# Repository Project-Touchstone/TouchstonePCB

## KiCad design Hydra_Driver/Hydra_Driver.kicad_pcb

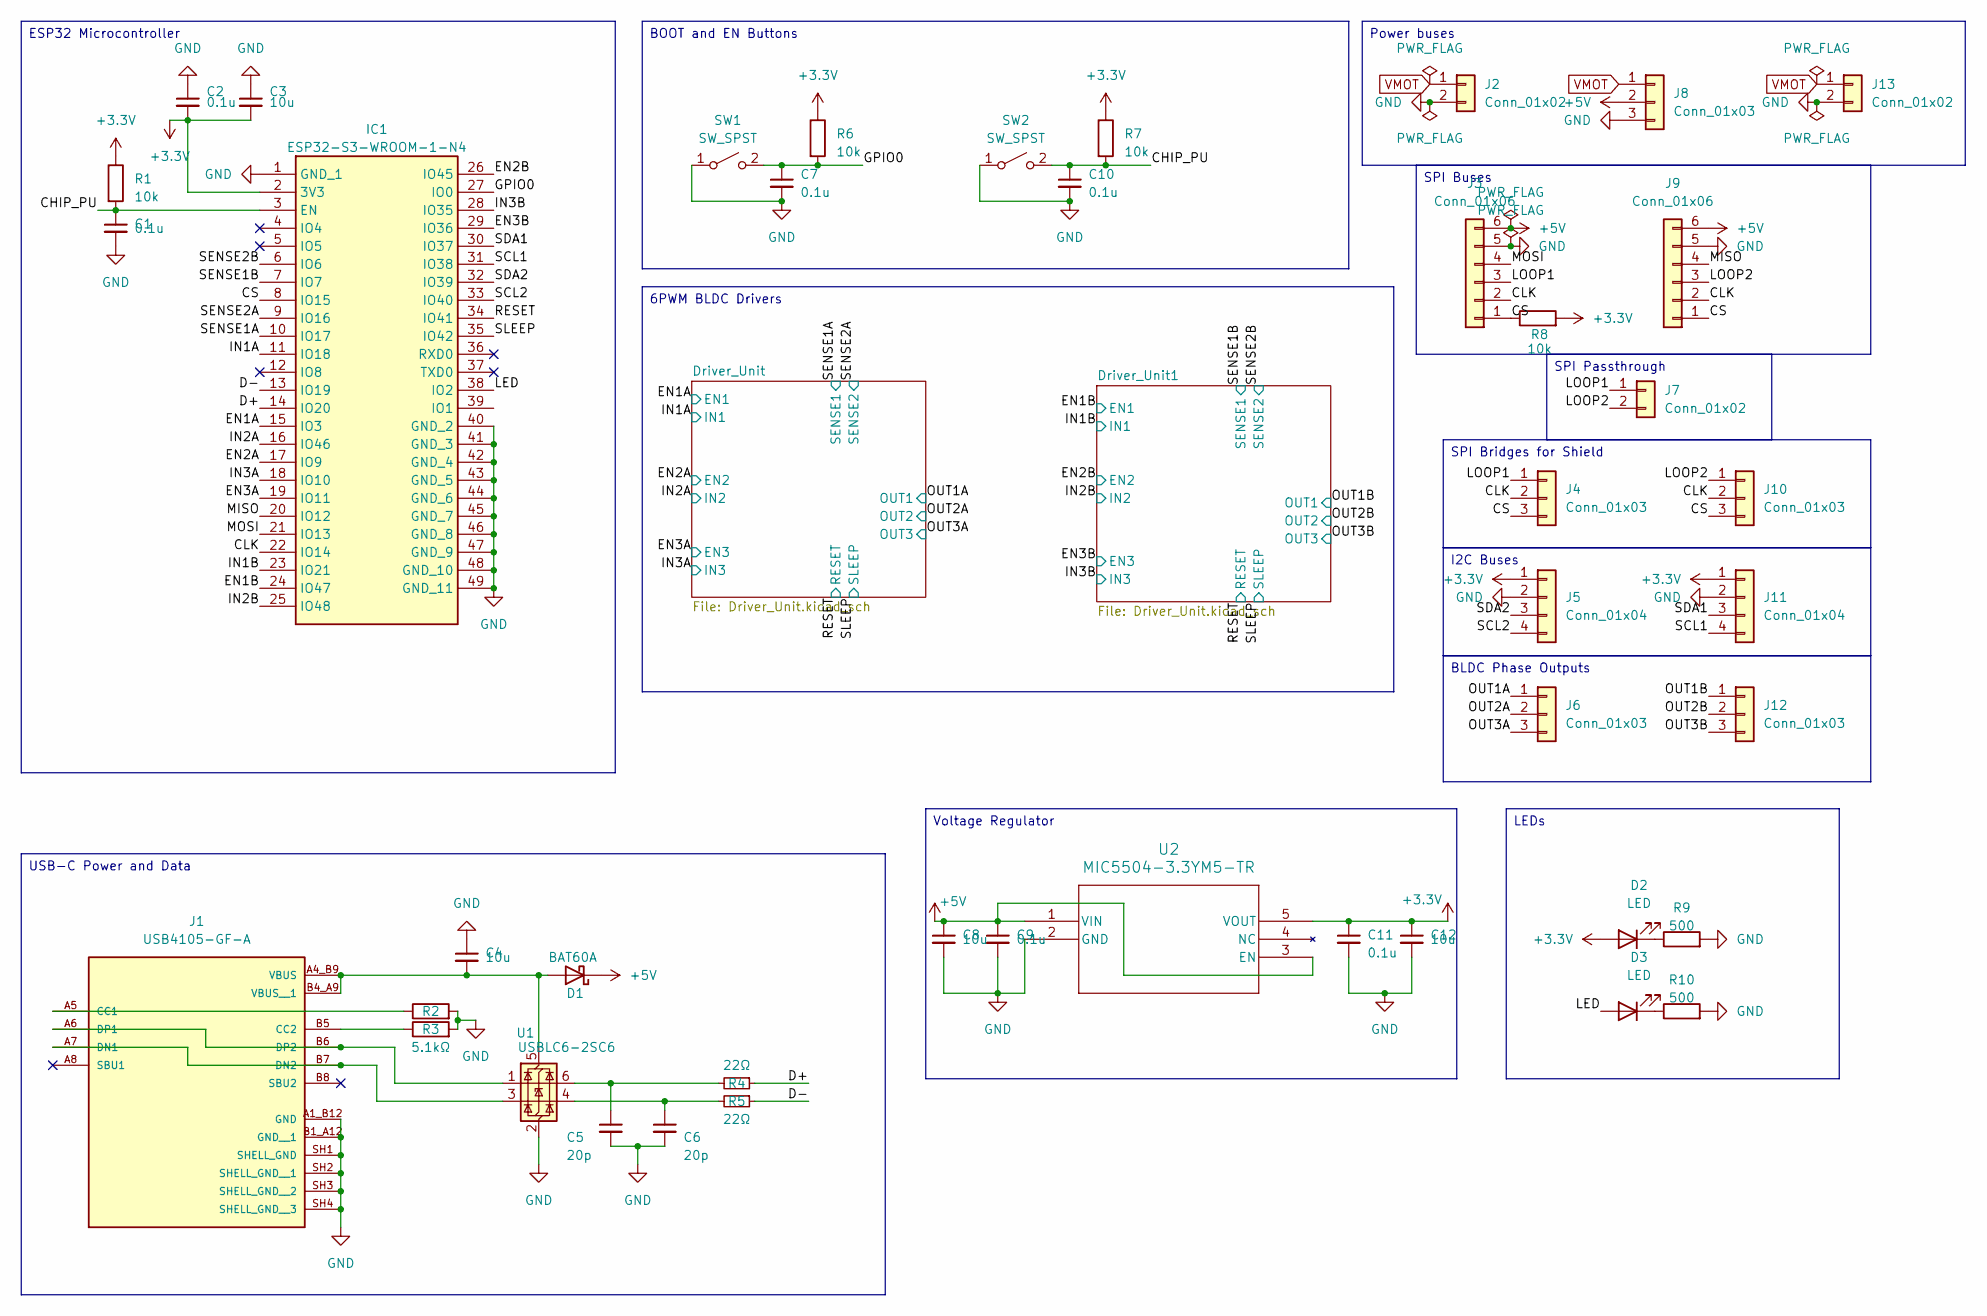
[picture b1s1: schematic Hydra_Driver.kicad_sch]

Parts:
C1, C2, C7, C9, C10, C11: 0.1u; C_0402_1005Metric
C3, C4, C8, C12: 10u; C_0805_2012Metric
C5, C6: 20p; C_0402_1005Metric; LCSC C1648
D1: BAT60A; D_SOD-323; JLCPCB C124187
D2, D3: LED; LED_0603_1608Metric
IC1: ESP32-S3-WROOM-1-N4; ESP32S3WROOM1N4; Manufacturer_Part_Number ESP32-S3-WROOM-1-N4; Mouser Part Number 356-ESP32-S3WROOM1N4
J1: USB4105-GF-A; GCT_USB4105-GF-A; PARTREV B4
J2, J13: Conn_01x02; TerminalBlock_MaiXu_MX126-5.0-02P_1x02_P5.00mm
J3: Conn_01x06; PinSocket_1x06_P2.54mm_Horizontal
J4, J8, J10: Conn_01x03; PinSocket_1x03_P2.54mm_Vertical
J5, J11: Conn_01x04; PinHeader_1x04_P2.54mm_Horizontal
J6, J12: Conn_01x03; PinHeader_1x03_P2.54mm_Horizontal
J7: Conn_01x02; PinHeader_1x02_P2.54mm_Vertical
J9: Conn_01x06; PinHeader_1x06_P2.54mm_Horizontal
R1, R6, R7, R8: 10k; R_0402_1005Metric
R2, R3: 5.1kΩ; R_0402_1005Metric; JLCPCB C23186
R4, R5: 22Ω; R_0402_1005Metric; LCSC C23345
R9, R10: 500; R_0402_1005Metric
SW1, SW2: SW_SPST; SW_PUSH_6mm
U1: USBLC6-2SC6; SOT-23-6; JLCPCB C2827654
U2: MIC5504-3.3YM5-TR; SOT-23-5_MC_MCH

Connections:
+3.3V: C2.2, C3.2, C11.1, C12.1, D2.2 (A), IC1.2 (3V3), J5.1, J11.1, R1.1, R6.1, R7.1, R8.2, U2.5 (VOUT); also elsewhere on the board
+5V: C8.1, C9.1, D1.1 (K), J3.6, J8.2, J9.6, U2.1 (VIN), U2.3 (EN)
/CHIP_PU: C1.1, C10.1, IC1.3 (EN), R1.2, R7.2, SW2.2 (B)
/CLK: IC1.22 (IO14), J3.2, J4.2, J9.2, J10.2
/CS: IC1.8 (IO15), J3.1, J4.3, J9.1, J10.3, R8.1
/D+: IC1.14 (IO20), R4.1
/D-: IC1.13 (IO19), R5.1
/EN1A: IC1.15 (IO3); also elsewhere on the board
/EN1B: IC1.24 (IO47); also elsewhere on the board
/EN2A: IC1.17 (IO9); also elsewhere on the board
/EN2B: IC1.26 (IO45); also elsewhere on the board
/EN3A: IC1.19 (IO11); also elsewhere on the board
/EN3B: IC1.29 (IO36); also elsewhere on the board
/GPIO0: C7.1, IC1.27 (IO0), R6.2, SW1.2 (B)
/IN1A: IC1.11 (IO18); also elsewhere on the board
/IN1B: IC1.23 (IO21); also elsewhere on the board
/IN2A: IC1.16 (IO46); also elsewhere on the board
/IN2B: IC1.25 (IO48); also elsewhere on the board
/IN3A: IC1.18 (IO10); also elsewhere on the board
/IN3B: IC1.28 (IO35); also elsewhere on the board
/LED: D3.2 (A), IC1.38 (IO2)
/LOOP1: J3.3, J4.1, J7.1
/LOOP2: J7.2, J9.3, J10.1
/MISO: IC1.20 (IO12), J9.4
/MOSI: IC1.21 (IO13), J3.4
/OUT1A: J6.1; also elsewhere on the board
/OUT1B: J12.1; also elsewhere on the board
/OUT2A: J6.2; also elsewhere on the board
/OUT2B: J12.2; also elsewhere on the board
/OUT3A: J6.3; also elsewhere on the board
/OUT3B: J12.3; also elsewhere on the board
/RESET: IC1.34 (IO41); also elsewhere on the board
/SCL1: IC1.31 (IO38), J11.4
/SCL2: IC1.33 (IO40), J5.4
/SDA1: IC1.30 (IO37), J11.3
/SDA2: IC1.32 (IO39), J5.3
/SENSE1A: IC1.10 (IO17); also elsewhere on the board
/SENSE1B: IC1.7 (IO7); also elsewhere on the board
/SENSE2A: IC1.9 (IO16); also elsewhere on the board
/SENSE2B: IC1.6 (IO6); also elsewhere on the board
/SLEEP: IC1.35 (IO42); also elsewhere on the board
GND: C1.2, C2.1, C3.1, C4.1, C5.2, C6.2, C7.2, C8.2, C9.2, C10.2, C11.2, C12.2, IC1.1 (GND_1), IC1.40 (GND_2), IC1.41 (GND_3), IC1.42 (GND_4), IC1.43 (GND_5), IC1.44 (GND_6), IC1.45 (GND_7), IC1.46 (GND_8), IC1.47 (GND_9), IC1.48 (GND_10), IC1.49 (GND_11), J1.A1_B12 (GND), J1.B1_A12 (GND__1), J1.SH1 (SHELL_GND), J1.SH2 (SHELL_GND__1), J1.SH3 (SHELL_GND__2), J1.SH4 (SHELL_GND__3), J2.2, J3.5, J5.2, J8.3, J9.5, J11.2, J13.2, R2.2, R3.2, R9.2, R10.2, SW1.1 (A), SW2.1 (A), U1.2 (GND), U2.2 (GND); also elsewhere on the board
unnamed: C5.1, R4.2, U1.6 (I/O1)
unnamed: C6.1, R5.2, U1.4 (I/O2)
unnamed: C4.2, D1.2 (A), J1.A4_B9 (VBUS), J1.B4_A9 (VBUS__1), U1.5 (VBUS)
unnamed: D2.1 (K), R9.1
unnamed: D3.1 (K), R10.1
unnamed: J1.A5 (CC1), R2.1
unnamed: J1.B5 (CC2), R3.1
unnamed: J1.A7 (DN1), J1.B7 (DN2), U1.3 (I/O2)
unnamed: J1.A6 (DP1), J1.B6 (DP2), U1.1 (I/O1)
VMOT: J2.1, J8.1, J13.1; also elsewhere on the board

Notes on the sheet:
BLDC Phase Outputs
SPI Bridges for Shield
I2C Buses
SPI Passthrough
Voltage Regulator
LEDs
ESP32 Microcontroller
BOOT and EN Buttons
SPI Buses
Power buses
6PWM BLDC Drivers
USB-C Power and Data

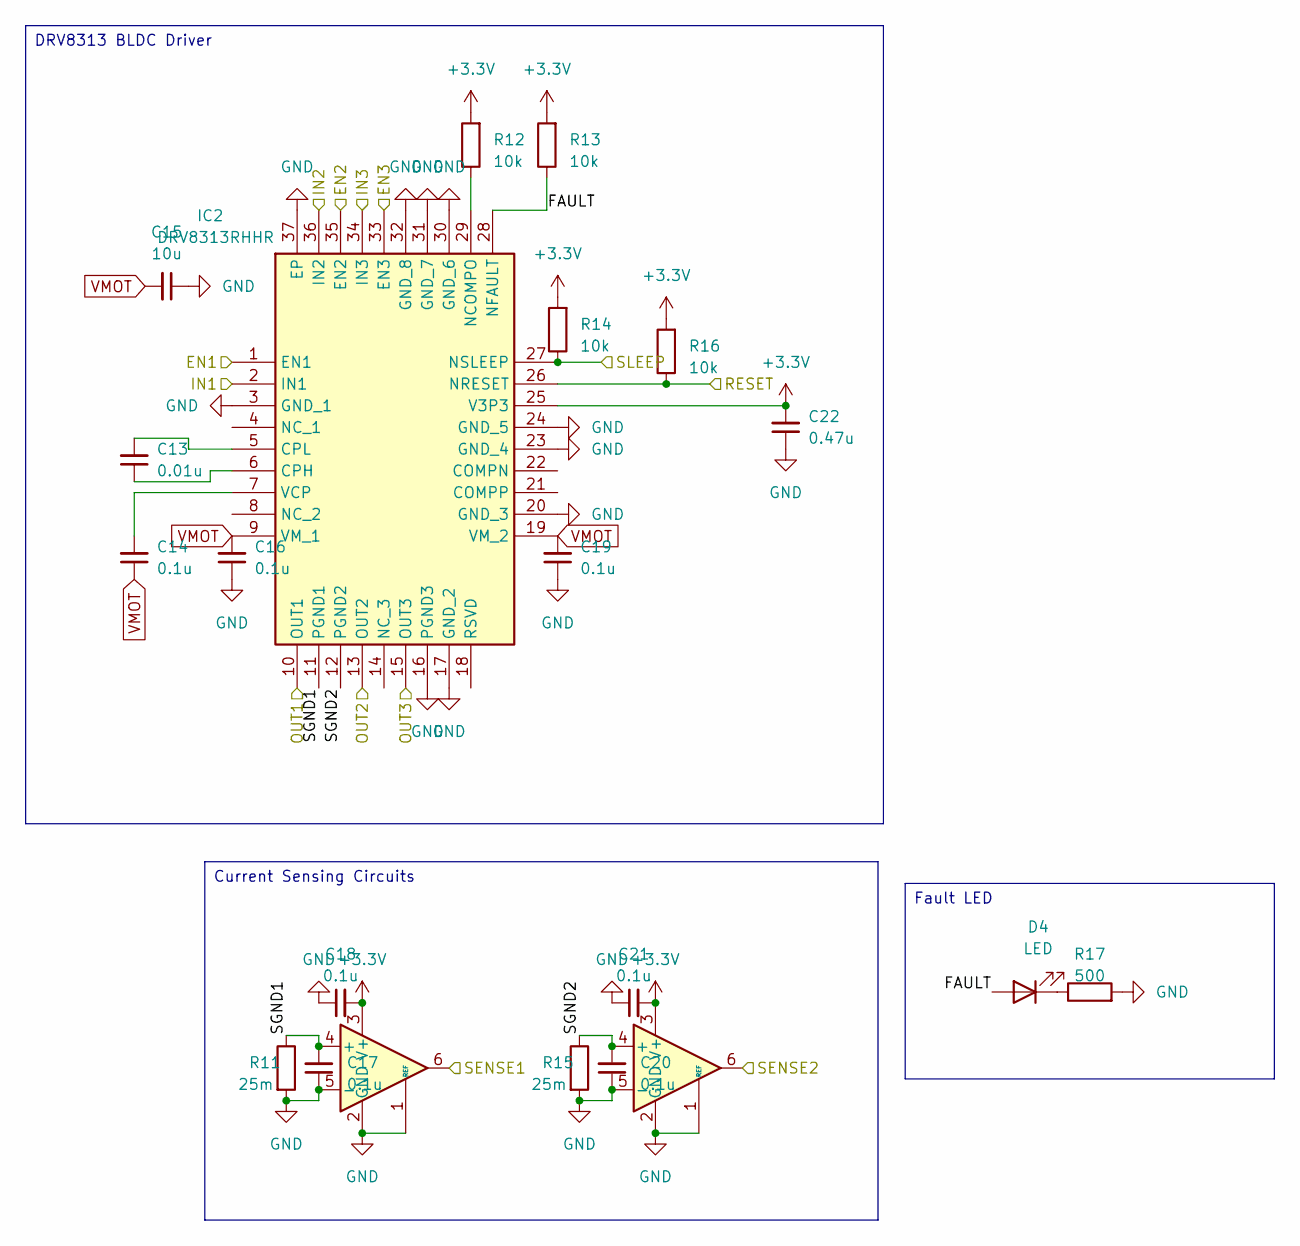
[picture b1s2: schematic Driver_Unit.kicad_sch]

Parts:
C13: 0.01u; C_0402_1005Metric
C14, C16, C17, C18, C19, C20, C21: 0.1u; C_0402_1005Metric
C15: 10u; C_0805_2012Metric
C22: 0.47u; C_0402_1005Metric
D4: LED; LED_0603_1608Metric
IC2: DRV8313RHHR; QFN50P600X600X100-37N-D; Manufacturer_Part_Number DRV8313RHHR; Mouser Part Number 595-DRV8313RHHR
R11, R15: 25m; R_0603_1608Metric
R12, R13, R14, R16: 10k; R_0402_1005Metric
R17: 500; R_0402_1005Metric
U3, U4: INA199xxDCK; SOT-363_SC-70-6

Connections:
+3.3V: C18.2, C21.2, C22.2, IC2.25 (V3P3), R12.2, R13.2, R14.2, R16.2, U3.3 (V+), U4.3 (V+); also elsewhere on the board
/Driver_Unit/FAULT: D4.2 (A), IC2.28 (NFAULT), R13.1
/Driver_Unit/SGND1: C17.2, IC2.11 (PGND1), R11.1, U3.4 (+)
/Driver_Unit/SGND2: C20.2, IC2.12 (PGND2), R15.1, U4.4 (+)
/EN1A: IC2.1 (EN1); also elsewhere on the board
/EN2A: IC2.35 (EN2); also elsewhere on the board
/EN3A: IC2.33 (EN3); also elsewhere on the board
/IN1A: IC2.2 (IN1); also elsewhere on the board
/IN2A: IC2.36 (IN2); also elsewhere on the board
/IN3A: IC2.34 (IN3); also elsewhere on the board
/OUT1A: IC2.10 (OUT1); also elsewhere on the board
/OUT2A: IC2.13 (OUT2); also elsewhere on the board
/OUT3A: IC2.15 (OUT3); also elsewhere on the board
/RESET: IC2.26 (NRESET), R16.1; also elsewhere on the board
/SENSE1A: U3.6; also elsewhere on the board
/SENSE2A: U4.6; also elsewhere on the board
/SLEEP: IC2.27 (NSLEEP), R14.1; also elsewhere on the board
GND: C15.1, C16.1, C17.1, C18.1, C19.1, C20.1, C21.1, C22.1, IC2.3 (GND_1), IC2.16 (PGND3), IC2.17 (GND_2), IC2.20 (GND_3), IC2.23 (GND_4), IC2.24 (GND_5), IC2.30 (GND_6), IC2.31 (GND_7), IC2.32 (GND_8), IC2.37 (EP), R11.2, R15.2, R17.2, U3.1 (REF), U3.2 (GND), U3.5 (-), U4.1 (REF), U4.2 (GND), U4.5 (-); also elsewhere on the board
unnamed: D4.1 (K), R17.1
unnamed: C13.1, IC2.6 (CPH)
unnamed: C13.2, IC2.5 (CPL)
unnamed: IC2.29 (NCOMPO), R12.1
unnamed: C14.2, IC2.7 (VCP)
VMOT: C14.1, C15.2, C16.2, C19.2, IC2.9 (VM_1), IC2.19 (VM_2); also elsewhere on the board

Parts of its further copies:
C23: 0.01u; C_0402_1005Metric
C24, C26, C27, C28, C29, C30, C31: 0.1u; C_0402_1005Metric
C25: 10u; C_0805_2012Metric
C32: 0.47u; C_0402_1005Metric
D5: LED; LED_0603_1608Metric
IC3: DRV8313RHHR; QFN50P600X600X100-37N-D; Manufacturer_Part_Number DRV8313RHHR; Mouser Part Number 595-DRV8313RHHR
R18, R22: 25m; R_0603_1608Metric
R19, R20, R21, R23: 10k; R_0402_1005Metric
R24: 500; R_0402_1005Metric
U5, U6: INA199xxDCK; SOT-363_SC-70-6

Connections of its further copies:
+3.3V: C28.2, C31.2, C32.2, IC3.25 (V3P3), R19.2, R20.2, R21.2, R23.2, U5.3 (V+), U6.3 (V+); also elsewhere on the board
/Driver_Unit1/FAULT: D5.2 (A), IC3.28 (NFAULT), R20.1
/Driver_Unit1/SGND1: C27.2, IC3.11 (PGND1), R18.1, U5.4 (+)
/Driver_Unit1/SGND2: C30.2, IC3.12 (PGND2), R22.1, U6.4 (+)
/EN1B: IC3.1 (EN1); also elsewhere on the board
/EN2B: IC3.35 (EN2); also elsewhere on the board
/EN3B: IC3.33 (EN3); also elsewhere on the board
/IN1B: IC3.2 (IN1); also elsewhere on the board
/IN2B: IC3.36 (IN2); also elsewhere on the board
/IN3B: IC3.34 (IN3); also elsewhere on the board
/OUT1B: IC3.10 (OUT1); also elsewhere on the board
/OUT2B: IC3.13 (OUT2); also elsewhere on the board
/OUT3B: IC3.15 (OUT3); also elsewhere on the board
/RESET: IC3.26 (NRESET), R23.1; also elsewhere on the board
/SENSE1B: U5.6; also elsewhere on the board
/SENSE2B: U6.6; also elsewhere on the board
/SLEEP: IC3.27 (NSLEEP), R21.1; also elsewhere on the board
GND: C25.1, C26.1, C27.1, C28.1, C29.1, C30.1, C31.1, C32.1, IC3.3 (GND_1), IC3.16 (PGND3), IC3.17 (GND_2), IC3.20 (GND_3), IC3.23 (GND_4), IC3.24 (GND_5), IC3.30 (GND_6), IC3.31 (GND_7), IC3.32 (GND_8), IC3.37 (EP), R18.2, R22.2, R24.2, U5.1 (REF), U5.2 (GND), U5.5 (-), U6.1 (REF), U6.2 (GND), U6.5 (-); also elsewhere on the board
unnamed: D5.1 (K), R24.1
unnamed: C23.1, IC3.6 (CPH)
unnamed: C23.2, IC3.5 (CPL)
unnamed: IC3.29 (NCOMPO), R19.1
unnamed: C24.2, IC3.7 (VCP)
VMOT: C24.1, C25.2, C26.2, C29.2, IC3.9 (VM_1), IC3.19 (VM_2); also elsewhere on the board

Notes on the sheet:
DRV8313 BLDC Driver
Fault LED
Current Sensing Circuits

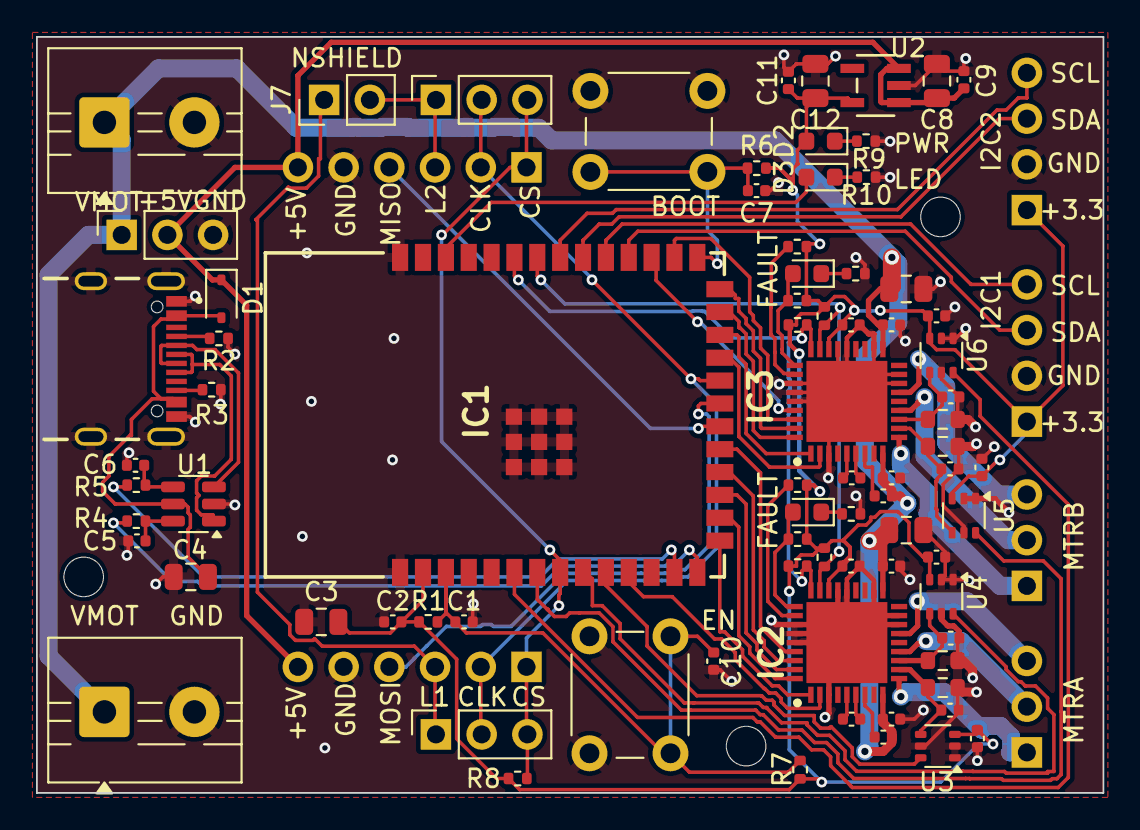
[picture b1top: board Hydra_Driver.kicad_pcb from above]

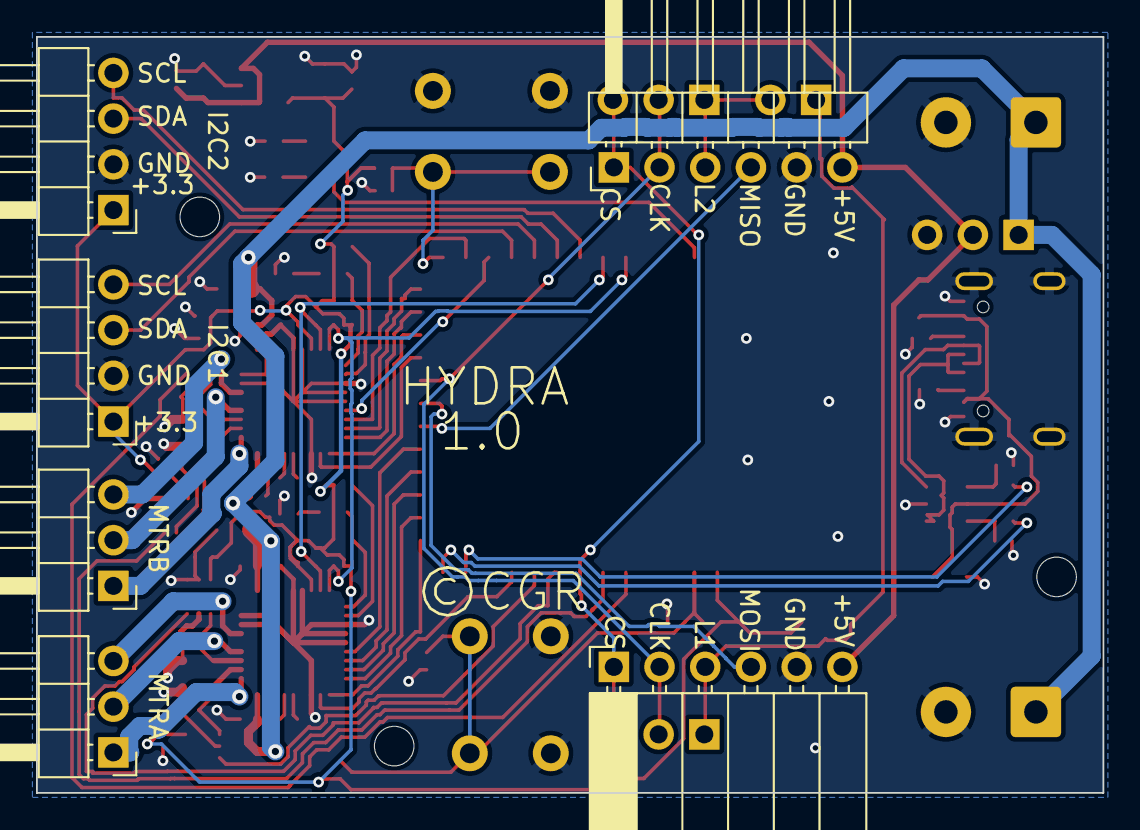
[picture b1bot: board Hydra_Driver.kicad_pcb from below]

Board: 2 copper layers, 59.2 x 42.0 mm, 85 parts (6 on the bottom side), 68 nets.

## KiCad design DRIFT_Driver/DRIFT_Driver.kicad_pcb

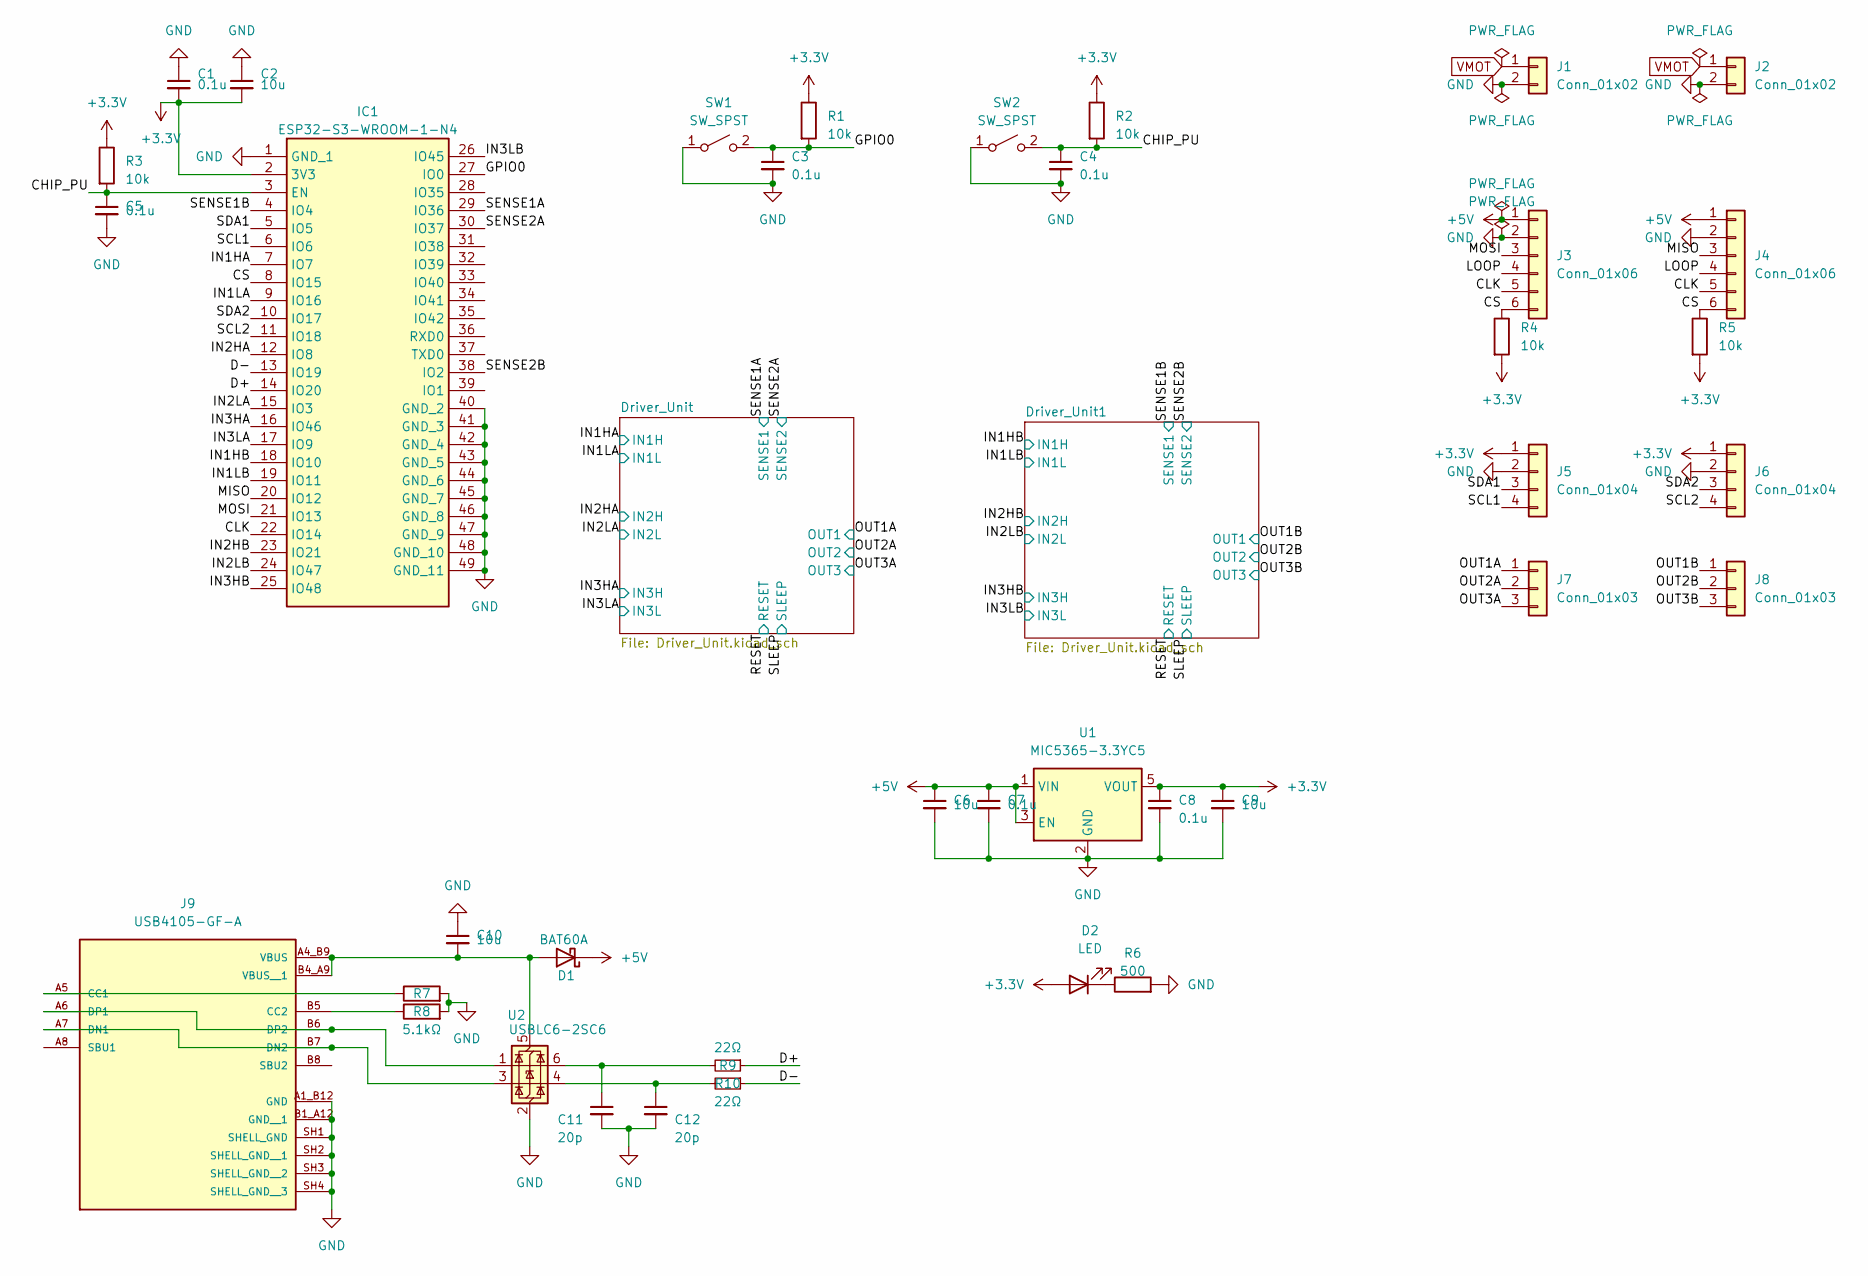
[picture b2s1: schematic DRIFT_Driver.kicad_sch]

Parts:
C1, C3, C4, C5, C7, C8: 0.1u; C_0402_1005Metric
C2, C6, C9, C10: 10u; C_0805_2012Metric
C11, C12: 20p; C_0402_1005Metric; LCSC C1648
D1: BAT60A; D_SOD-323; JLCPCB C124187
D2: LED; LED_0603_1608Metric
IC1: ESP32-S3-WROOM-1-N4; ESP32S3WROOM1N4; Manufacturer_Part_Number ESP32-S3-WROOM-1-N4; Mouser Part Number 356-ESP32-S3WROOM1N4
J1, J2: Conn_01x02; TerminalBlock_MaiXu_MX126-5.0-02P_1x02_P5.00mm
J3: Conn_01x06; PinSocket_1x06_P2.54mm_Horizontal
J4: Conn_01x06; PinHeader_1x06_P2.54mm_Horizontal
J5, J6: Conn_01x04; PinHeader_1x04_P2.54mm_Vertical
J7, J8: Conn_01x03; PinHeader_1x03_P2.54mm_Vertical
J9: USB4105-GF-A; GCT_USB4105-GF-A; PARTREV B4
R1, R2, R3, R4, R5: 10k; R_0402_1005Metric
R6: 500; R_0402_1005Metric
R7: 5.1kΩ; R_0402_1005Metric_Pad0.72x0.64mm_HandSolder; JLCPCB C23186
R8: 5.1kΩ; R_0402_1005Metric; JLCPCB C23186
R9, R10: 22Ω; R_0402_1005Metric; LCSC C23345
SW1, SW2: SW_SPST; SW_PUSH_6mm
U1: MIC5365-3.3YC5; SOT-353_SC-70-5
U2: USBLC6-2SC6; SOT-23-6; JLCPCB C2827654

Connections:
+3.3V: C1.2, C2.2, C8.1, C9.1, D2.2 (A), IC1.2 (3V3), J5.1, J6.1, R1.1, R2.1, R3.1, R4.2, R5.2, U1.5 (VOUT); also elsewhere on the board
+5V: C6.1, C7.1, D1.1 (K), J3.1, J4.1, U1.1 (VIN), U1.3 (EN)
/CHIP_PU: C4.1, C5.1, IC1.3 (EN), R2.2, R3.2, SW2.2 (B)
/CLK: IC1.22 (IO14), J3.5, J4.5
/CS: IC1.8 (IO15), J3.6, J4.6, R4.1, R5.1
/D+: IC1.14 (IO20), R9.1
/D-: IC1.13 (IO19), R10.1
/GPIO0: C3.1, IC1.27 (IO0), R1.2, SW1.2 (B)
/IN1HA: IC1.7 (IO7); also elsewhere on the board
/IN1HB: IC1.18 (IO10); also elsewhere on the board
/IN1LA: IC1.9 (IO16); also elsewhere on the board
/IN1LB: IC1.19 (IO11); also elsewhere on the board
/IN2HA: IC1.12 (IO8); also elsewhere on the board
/IN2HB: IC1.23 (IO21); also elsewhere on the board
/IN2LA: IC1.15 (IO3); also elsewhere on the board
/IN2LB: IC1.24 (IO47); also elsewhere on the board
/IN3HA: IC1.16 (IO46); also elsewhere on the board
/IN3HB: IC1.25 (IO48); also elsewhere on the board
/IN3LA: IC1.17 (IO9); also elsewhere on the board
/IN3LB: IC1.26 (IO45); also elsewhere on the board
/LOOP: J3.4, J4.4
/MISO: IC1.20 (IO12), J4.3
/MOSI: IC1.21 (IO13), J3.3
/OUT1A: J7.1; also elsewhere on the board
/OUT1B: J8.1; also elsewhere on the board
/OUT2A: J7.2; also elsewhere on the board
/OUT2B: J8.2; also elsewhere on the board
/OUT3A: J7.3; also elsewhere on the board
/OUT3B: J8.3; also elsewhere on the board
/SCL1: IC1.6 (IO6), J5.4
/SCL2: IC1.11 (IO18), J6.4
/SDA1: IC1.5 (IO5), J5.3
/SDA2: IC1.10 (IO17), J6.3
/SENSE1A: IC1.29 (IO36); also elsewhere on the board
/SENSE1B: IC1.4 (IO4); also elsewhere on the board
/SENSE2A: IC1.30 (IO37); also elsewhere on the board
/SENSE2B: IC1.38 (IO2); also elsewhere on the board
GND: C1.1, C2.1, C3.2, C4.2, C5.2, C6.2, C7.2, C8.2, C9.2, C10.1, C11.2, C12.2, IC1.1 (GND_1), IC1.40 (GND_2), IC1.41 (GND_3), IC1.42 (GND_4), IC1.43 (GND_5), IC1.44 (GND_6), IC1.45 (GND_7), IC1.46 (GND_8), IC1.47 (GND_9), IC1.48 (GND_10), IC1.49 (GND_11), J1.2, J2.2, J3.2, J4.2, J5.2, J6.2, J9.A1_B12 (GND), J9.B1_A12 (GND__1), J9.SH1 (SHELL_GND), J9.SH2 (SHELL_GND__1), J9.SH3 (SHELL_GND__2), J9.SH4 (SHELL_GND__3), R6.2, R7.2, R8.2, SW1.1 (A), SW2.1 (A), U1.2 (GND), U2.2 (GND); also elsewhere on the board
unnamed: C11.1, R9.2, U2.6 (I/O1)
unnamed: C12.1, R10.2, U2.4 (I/O2)
unnamed: C10.2, D1.2 (A), J9.A4_B9 (VBUS), J9.B4_A9 (VBUS__1), U2.5 (VBUS)
unnamed: D2.1 (K), R6.1
unnamed: J9.A5 (CC1), R7.1
unnamed: J9.B5 (CC2), R8.1
unnamed: J9.A7 (DN1), J9.B7 (DN2), U2.3 (I/O2)
unnamed: J9.A6 (DP1), J9.B6 (DP2), U2.1 (I/O1)
VMOT: J1.1, J2.1; also elsewhere on the board

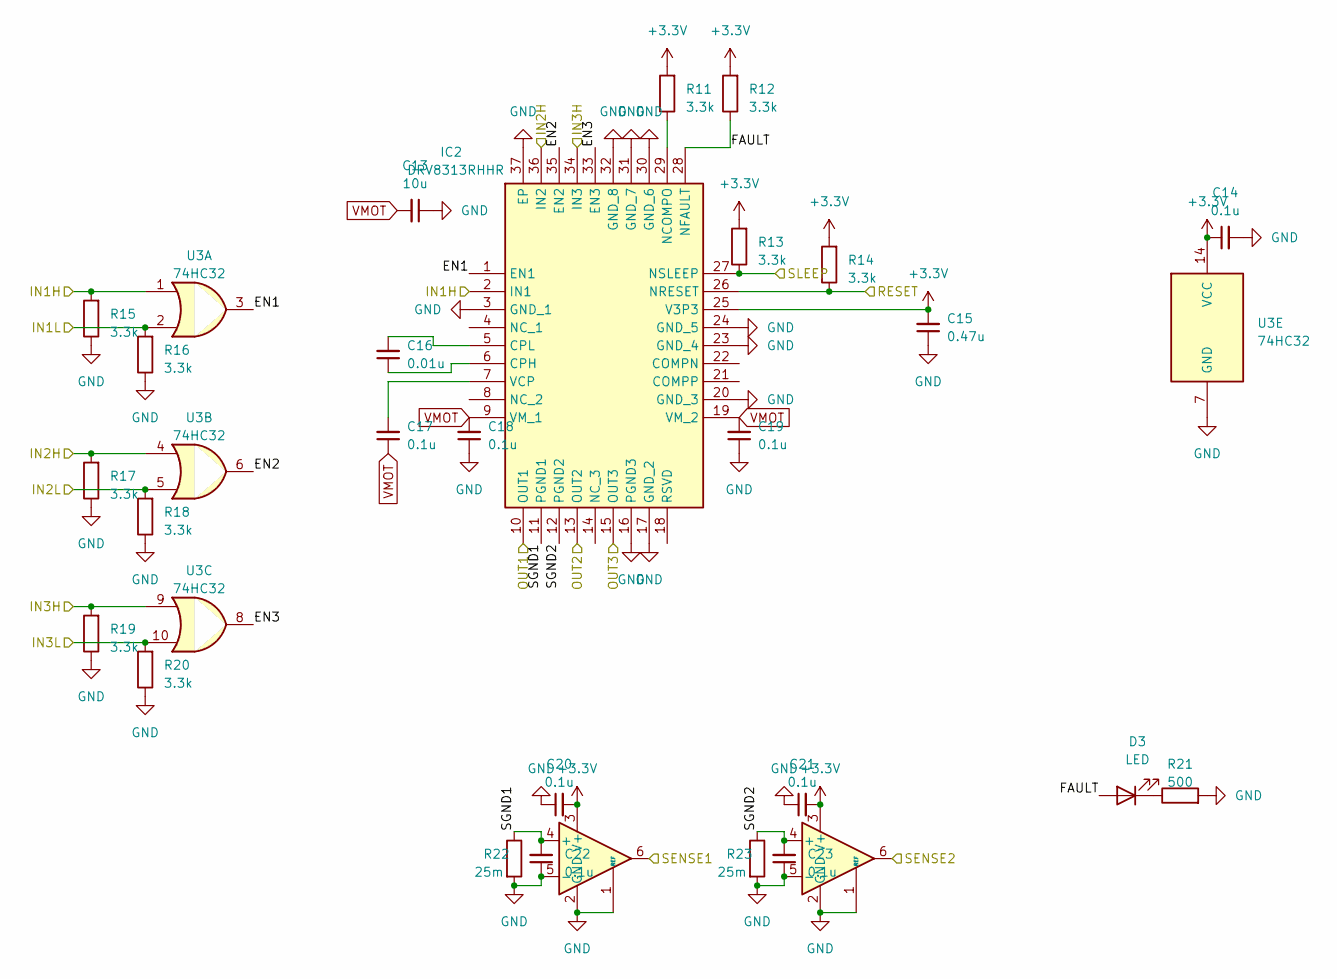
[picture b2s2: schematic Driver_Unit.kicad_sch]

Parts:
C13: 10u; C_0805_2012Metric
C14, C17, C18, C19, C20, C21, C22, C23: 0.1u; C_0402_1005Metric
C15: 0.47u; C_0402_1005Metric
C16: 0.01u; C_0402_1005Metric
D3: LED; LED_0603_1608Metric
IC2: DRV8313RHHR; QFN50P600X600X100-37N-D; Manufacturer_Part_Number DRV8313RHHR; Mouser Part Number 595-DRV8313RHHR
R11, R12, R13, R14, R15, R16, R17, R18, R19, R20: 3.3k; R_0402_1005Metric
R21: 500; R_0402_1005Metric
R22, R23: 25m; R_0603_1608Metric
U3: 74HC32; SOIC-14_3.9x8.7mm_P1.27mm
U4, U5: INA199xxDCK; SOT-363_SC-70-6

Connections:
+3.3V: C14.1, C15.2, C20.2, C21.2, IC2.25 (V3P3), R11.2, R12.2, R13.2, R14.2, U3.14 (VCC), U4.3 (V+), U5.3 (V+); also elsewhere on the board
/Driver_Unit/EN1: IC2.1 (EN1), U3.3
/Driver_Unit/EN2: IC2.35 (EN2), U3.6
/Driver_Unit/EN3: IC2.33 (EN3), U3.8
/Driver_Unit/FAULT: D3.2 (A), IC2.28 (NFAULT), R12.1
/Driver_Unit/SGND1: C22.2, IC2.11 (PGND1), R22.1, U4.4 (+)
/Driver_Unit/SGND2: C23.2, IC2.12 (PGND2), R23.1, U5.4 (+)
/IN1HA: IC2.2 (IN1), R15.2, U3.1; also elsewhere on the board
/IN1LA: R16.2, U3.2; also elsewhere on the board
/IN2HA: IC2.36 (IN2), R17.2, U3.4; also elsewhere on the board
/IN2LA: R18.2, U3.5; also elsewhere on the board
/IN3HA: IC2.34 (IN3), R19.2, U3.9; also elsewhere on the board
/IN3LA: R20.2, U3.10; also elsewhere on the board
/OUT1A: IC2.10 (OUT1); also elsewhere on the board
/OUT2A: IC2.13 (OUT2); also elsewhere on the board
/OUT3A: IC2.15 (OUT3); also elsewhere on the board
/RESET: IC2.26 (NRESET), R14.1; also elsewhere on the board
/SENSE1A: U4.6; also elsewhere on the board
/SENSE2A: U5.6; also elsewhere on the board
/SLEEP: IC2.27 (NSLEEP), R13.1; also elsewhere on the board
GND: C13.1, C14.2, C15.1, C18.1, C19.1, C20.1, C21.1, C22.1, C23.1, IC2.3 (GND_1), IC2.16 (PGND3), IC2.17 (GND_2), IC2.20 (GND_3), IC2.23 (GND_4), IC2.24 (GND_5), IC2.30 (GND_6), IC2.31 (GND_7), IC2.32 (GND_8), IC2.37 (EP), R15.1, R16.1, R17.1, R18.1, R19.1, R20.1, R21.2, R22.2, R23.2, U3.7 (GND), U4.1 (REF), U4.2 (GND), U4.5 (-), U5.1 (REF), U5.2 (GND), U5.5 (-); also elsewhere on the board
unnamed: D3.1 (K), R21.1
unnamed: C16.1, IC2.6 (CPH)
unnamed: C16.2, IC2.5 (CPL)
unnamed: IC2.29 (NCOMPO), R11.1
unnamed: C17.2, IC2.7 (VCP)
VMOT: C13.2, C17.1, C18.2, C19.2, IC2.9 (VM_1), IC2.19 (VM_2); also elsewhere on the board

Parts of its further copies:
C24: 10u; C_0805_2012Metric
C25, C28, C29, C30, C31, C32, C33, C34: 0.1u; C_0402_1005Metric
C26: 0.47u; C_0402_1005Metric
C27: 0.01u; C_0402_1005Metric
D4: LED; LED_0603_1608Metric
IC3: DRV8313RHHR; QFN50P600X600X100-37N-D; Manufacturer_Part_Number DRV8313RHHR; Mouser Part Number 595-DRV8313RHHR
R24, R25, R26, R27, R28, R29, R30, R31, R32, R33: 3.3k; R_0402_1005Metric
R34: 500; R_0402_1005Metric
R35, R36: 25m; R_0603_1608Metric
U6: 74HC32; SOIC-14_3.9x8.7mm_P1.27mm
U7, U8: INA199xxDCK; SOT-363_SC-70-6

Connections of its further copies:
+3.3V: C25.1, C26.2, C31.2, C32.2, IC3.25 (V3P3), R24.2, R25.2, R26.2, R27.2, U6.14 (VCC), U7.3 (V+), U8.3 (V+); also elsewhere on the board
/Driver_Unit1/EN1: IC3.1 (EN1), U6.3
/Driver_Unit1/EN2: IC3.35 (EN2), U6.6
/Driver_Unit1/EN3: IC3.33 (EN3), U6.8
/Driver_Unit1/FAULT: D4.2 (A), IC3.28 (NFAULT), R25.1
/Driver_Unit1/SGND1: C33.2, IC3.11 (PGND1), R35.1, U7.4 (+)
/Driver_Unit1/SGND2: C34.2, IC3.12 (PGND2), R36.1, U8.4 (+)
/IN1HB: IC3.2 (IN1), R28.2, U6.1; also elsewhere on the board
/IN1LB: R29.2, U6.2; also elsewhere on the board
/IN2HB: IC3.36 (IN2), R30.2, U6.4; also elsewhere on the board
/IN2LB: R31.2, U6.5; also elsewhere on the board
/IN3HB: IC3.34 (IN3), R32.2, U6.9; also elsewhere on the board
/IN3LB: R33.2, U6.10; also elsewhere on the board
/OUT1B: IC3.10 (OUT1); also elsewhere on the board
/OUT2B: IC3.13 (OUT2); also elsewhere on the board
/OUT3B: IC3.15 (OUT3); also elsewhere on the board
/RESET: IC3.26 (NRESET), R27.1; also elsewhere on the board
/SENSE1B: U7.6; also elsewhere on the board
/SENSE2B: U8.6; also elsewhere on the board
/SLEEP: IC3.27 (NSLEEP), R26.1; also elsewhere on the board
GND: C24.1, C25.2, C26.1, C29.1, C30.1, C31.1, C32.1, C33.1, C34.1, IC3.3 (GND_1), IC3.16 (PGND3), IC3.17 (GND_2), IC3.20 (GND_3), IC3.23 (GND_4), IC3.24 (GND_5), IC3.30 (GND_6), IC3.31 (GND_7), IC3.32 (GND_8), IC3.37 (EP), R28.1, R29.1, R30.1, R31.1, R32.1, R33.1, R34.2, R35.2, R36.2, U6.7 (GND), U7.1 (REF), U7.2 (GND), U7.5 (-), U8.1 (REF), U8.2 (GND), U8.5 (-); also elsewhere on the board
unnamed: D4.1 (K), R34.1
unnamed: C27.1, IC3.6 (CPH)
unnamed: C27.2, IC3.5 (CPL)
unnamed: IC3.29 (NCOMPO), R24.1
unnamed: C28.2, IC3.7 (VCP)
VMOT: C24.2, C28.1, C29.2, C30.2, IC3.9 (VM_1), IC3.19 (VM_2); also elsewhere on the board

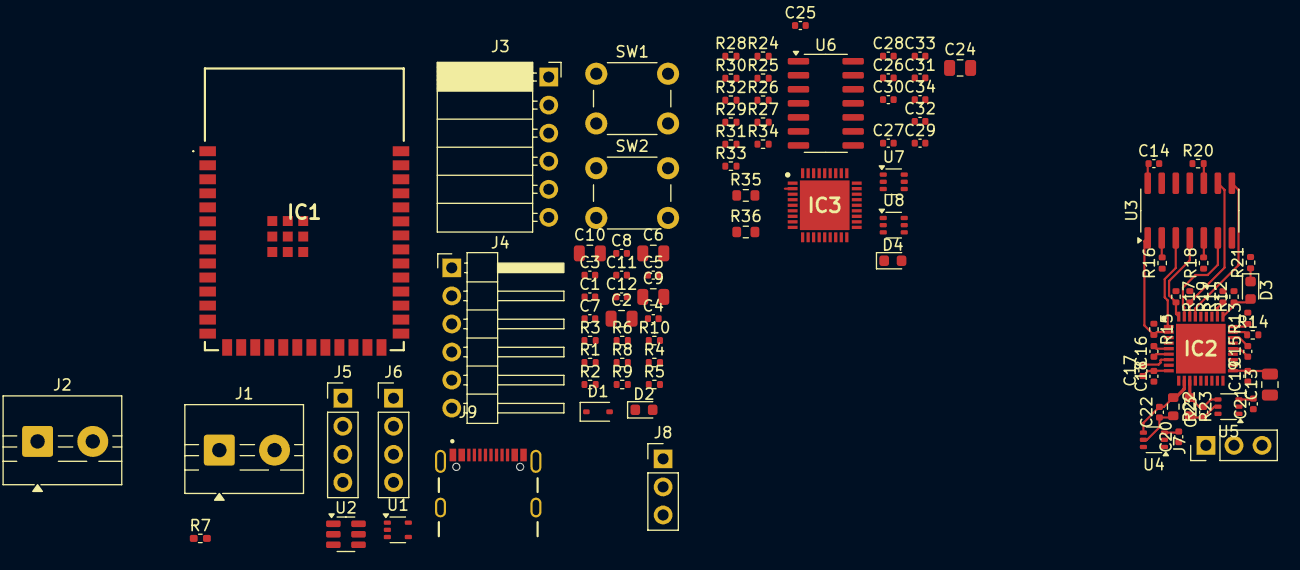
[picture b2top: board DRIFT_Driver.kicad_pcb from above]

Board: 2 copper layers, 96 parts (0 on the bottom side), 71 nets.

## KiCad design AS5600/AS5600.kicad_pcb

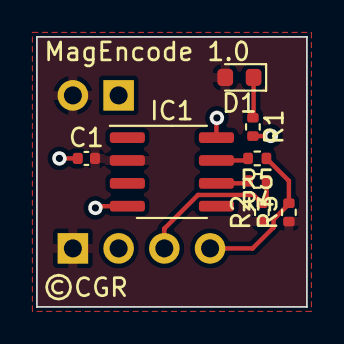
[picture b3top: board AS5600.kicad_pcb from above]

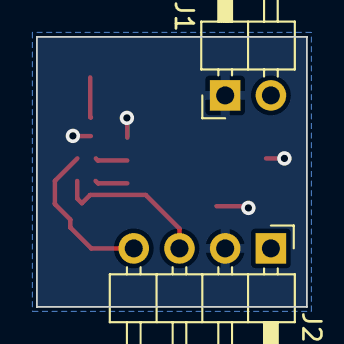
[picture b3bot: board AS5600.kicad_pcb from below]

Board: 2 copper layers, 15.0 x 15.0 mm, 10 parts (2 on the bottom side), 7 nets.

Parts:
C1: 0.1uF; C_0402_1005Metric
D1: LED; LED_0603_1608Metric
IC1: AS5600-ASOT; SOIC-8_3.9x4.9mm_P1.27mm
J1: Conn_01x02; PinHeader_1x02_P2.54mm_Horizontal
J2: Conn_01x04; PinHeader_1x04_P2.54mm_Horizontal
R1: 500; R_0402_1005Metric
R2, R3: 1.2K; R_0402_1005Metric
R4, R5: 100; R_0402_1005Metric

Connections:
/SCL: J2.4, R3.2, R5.1
/SDA: J2.3, R2.2, R4.1
/VCC: C1.2, D1.2 (A), IC1.2 (VDD3V3), J1.2, J2.1, R2.1, R3.1
GND: C1.1, IC1.4 (GND), IC1.8 (DIR), J1.1, J2.2, R1.2
unnamed: D1.1 (K), R1.1
unnamed: IC1.7 (SCL), R5.2
unnamed: IC1.6 (SDA), R4.2

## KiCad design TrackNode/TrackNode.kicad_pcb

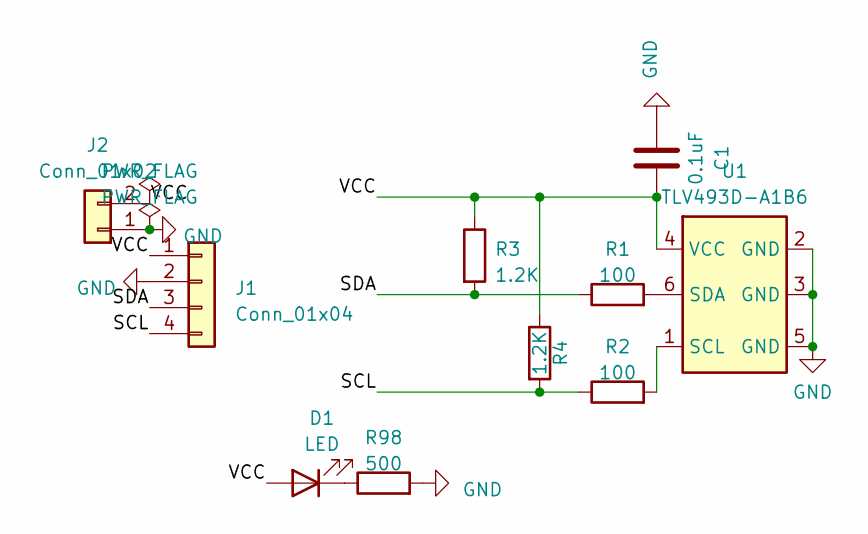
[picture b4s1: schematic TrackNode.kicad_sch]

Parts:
C1: 0.1uF; C_0402_1005Metric
D1: LED; LED_0603_1608Metric
J1: Conn_01x04; PinHeader_1x04_P2.54mm_Vertical
J2: Conn_01x02; PinHeader_1x02_P2.54mm_Horizontal
R1, R2: 100; R_0402_1005Metric
R3, R4: 1.2K; R_0402_1005Metric
R98: 500; R_0402_1005Metric
U1: TLV493D-A1B6; TSOP-6_1.65x3.05mm_P0.95mm

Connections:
/SCL: J1.4, R2.1, R4.2
/SDA: J1.3, R1.1, R3.2
/VCC: C1.2, D1.2 (A), J1.1, J2.2, R3.1, R4.1, U1.4 (VCC)
GND: C1.1, J1.2, J2.1, U1.2 (GND), U1.3 (GND), U1.5 (GND); also elsewhere on the board
unnamed 4: D1.1 (K); also elsewhere on the board
unnamed: R2.2, U1.1 (SCL)
unnamed: R1.2, U1.6 (SDA)

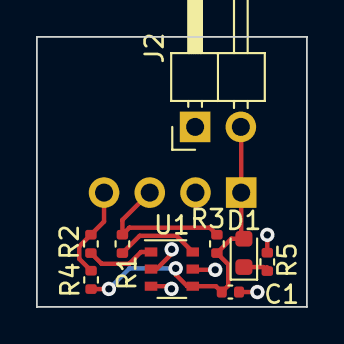
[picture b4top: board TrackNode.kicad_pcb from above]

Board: 2 copper layers, 15.0 x 15.0 mm, 10 parts (1 on the bottom side), 7 nets.

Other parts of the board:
R5: 500; R_0402_1005Metric

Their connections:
GND: R5.2; also elsewhere on the board
unnamed 4: R5.1; also elsewhere on the board

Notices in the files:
AS5600/AS5600.kicad_pcb:
©CGR
